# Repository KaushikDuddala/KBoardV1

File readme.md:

# KBoard

The KBoard is a simple RP2040 devboard designed from the guide!! I made some changes visually like the orientation of the chip bc lowk 45 degrees looks cooler. routing was a nightmate tho!!

## Features:

- RP2040 microcontroller  
- USB-C connector for programming/power  
- Standard pin headers

## Future Features:

- Convert to a BadUSB design
- Wi-Fi/BT support  
- Battery Support?

## Final Design

## PCB Design

## Bill of Materials (BOM)

A combined BOM including JLCPCB part numbers:

|Id|Designator|Footprint|Quantity|Designation|Supplier & Ref|JLCPCB Part #|Unit Price|
|--|----------|---------|--------|-----------|---------------|------------|----------|
|1|J3,J2|PinHeader_1x20_P2.54mm_Vertical|2|Conn_01x20||| |
|2|U1|QFN-56-1EP_7x7mm_P0.4mm_EP3.2x3.2mm|1|RP2040||C2040|$1.8330|
|3|U3|Winbond_USON-8-1EP_3x2mm_P0.5mm_EP0.2x1.6mm|1|W25Q128JVS||C2843335|$1.1730|
|4|C8,C5,C2,C11,C17,C12,C9,C7,C6,C4,C3|C_0402_1005Metric|11|0.1uF||C1525|$0.0264|
|5|R5,R7|R_0402_1005Metric|2|1K||C11702|$0.0024|
|6|C16,C15|C_0402_1005Metric|2|33pF||C1562|$0.0040|
|7|Y1|Crystal_SMD_3225-4Pin_3.2x2.5mm|1|12 MHz||C9002|$0.1290|
|8|U2|SOT-23|1|MCP1700x-330xxTT||C39051|$1.9695|
|9|SW1|SW_Push_SPST_NO_Alps_SKRK|1|SW_Push||C720477|$0.0850|
|10|R6|R_0402_1005Metric|1|10K||C25744|$0.0010|
|11|R4,R3|R_0402_1005Metric|2|27||C25100|$0.0120|
|12|R2,R1|R_0402_1005Metric|2|5.1k||C25905|$0.0020|
|13|J4|PinHeader_1x03_P2.54mm_Vertical|1|Conn_01x03||| |
|14|C14,C13|C_0402_1005Metric|2|10uF||C19702|$0.0224|
|15|C10,C1|C_0402_1005Metric|2|1uF||C52923|$0.0116|
|16|J1|USB_C_Receptacle_HRO_TYPE-C-31-M-12|1|USB_C_Receptacle_USB2.0_14P||C165948|$0.3388|

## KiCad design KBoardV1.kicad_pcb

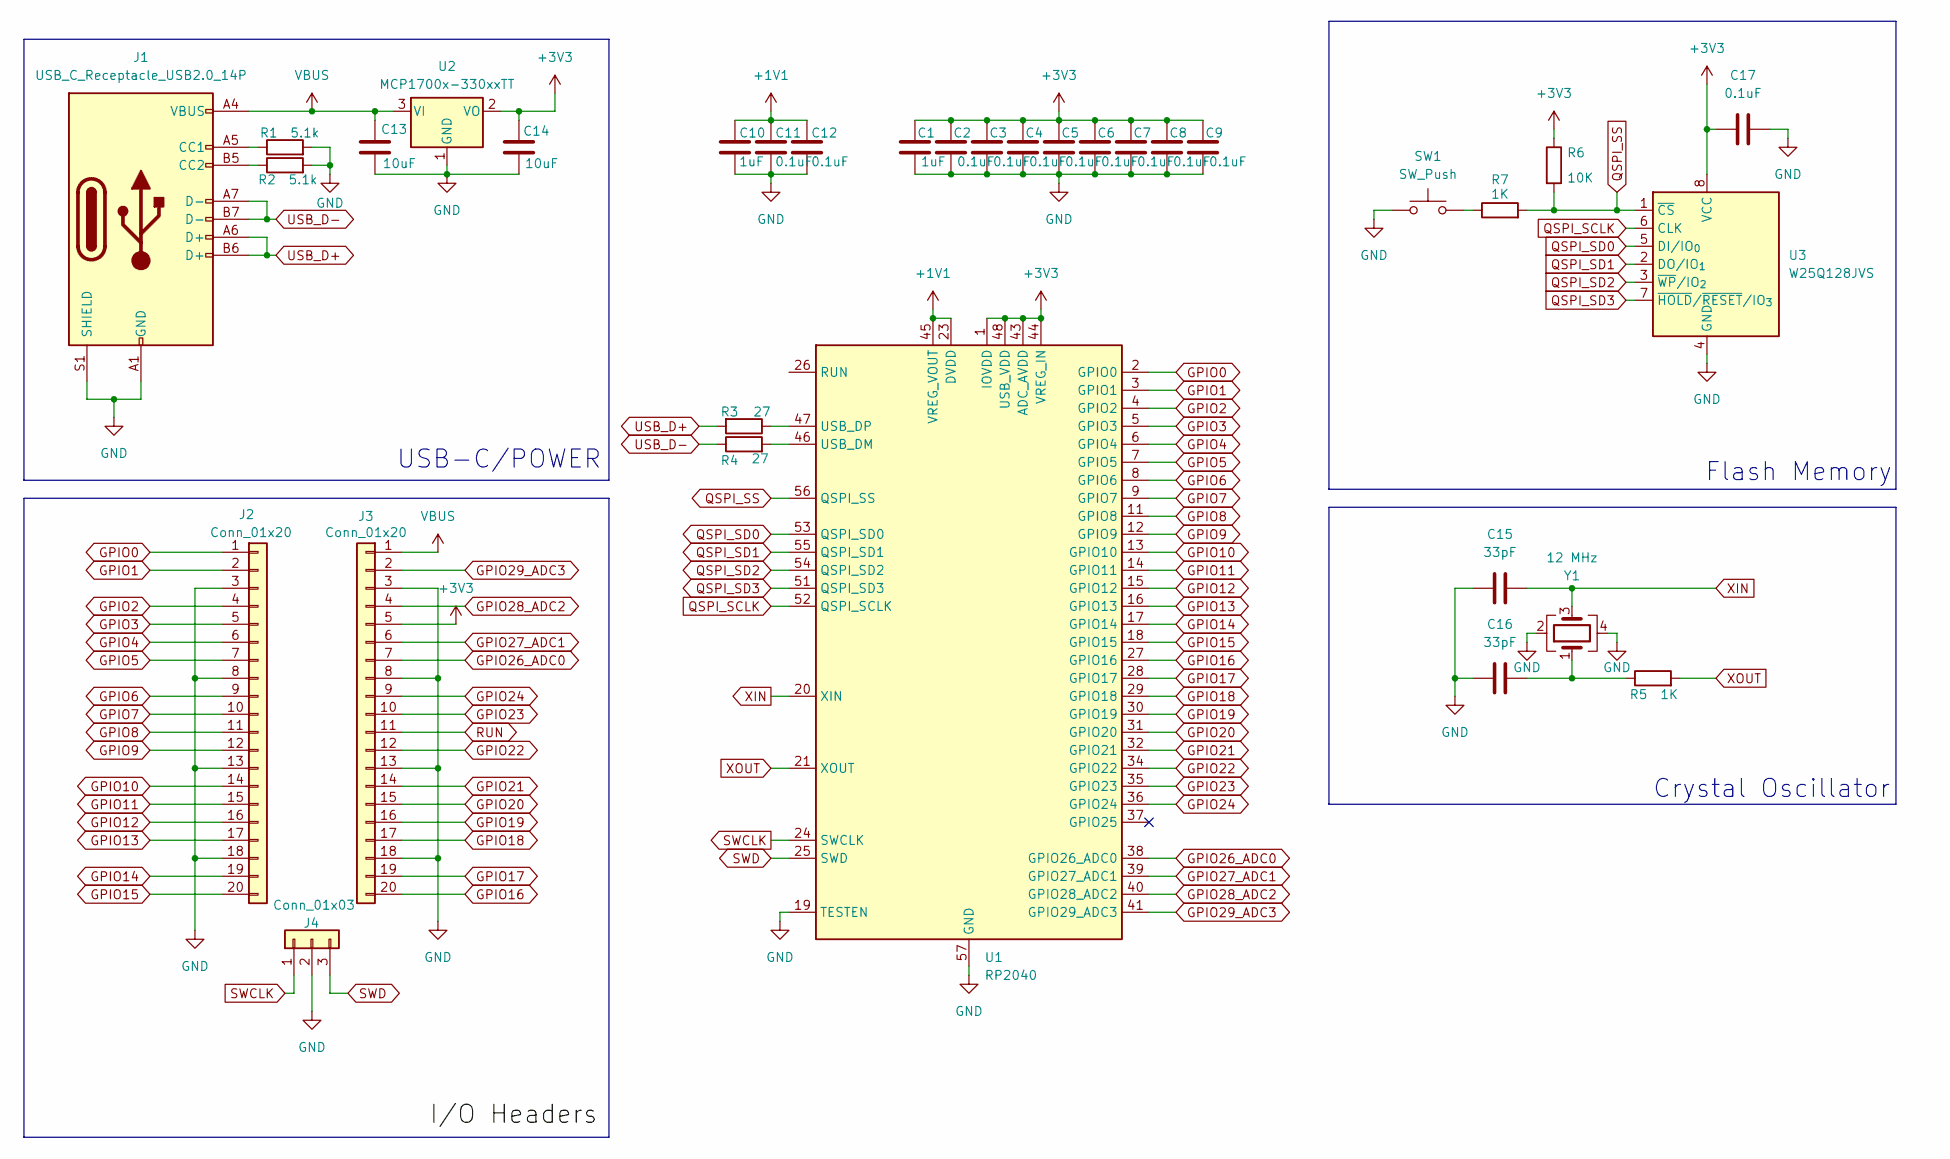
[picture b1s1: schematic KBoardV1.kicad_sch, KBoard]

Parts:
C1, C10: 1uF; C_0402_1005Metric
C2, C3, C4, C5, C6, C7, C8, C9, C11, C12, C17: 0.1uF; C_0402_1005Metric
C13, C14: 10uF; C_0402_1005Metric
C15, C16: 33pF; C_0402_1005Metric
J1: USB_C_Receptacle_USB2.0_14P; USB_C_Receptacle_HRO_TYPE-C-31-M-12
J2, J3: Conn_01x20; PinHeader_1x20_P2.54mm_Vertical
J4: Conn_01x03; PinHeader_1x03_P2.54mm_Vertical
R1, R2: 5.1k; R_0402_1005Metric
R3, R4: 27; R_0402_1005Metric
R5, R7: 1K; R_0402_1005Metric
R6: 10K; R_0402_1005Metric
SW1: SW_Push; SW_Push_SPST_NO_Alps_SKRK
U1: RP2040; QFN-56-1EP_7x7mm_P0.4mm_EP3.2x3.2mm
U2: MCP1700x-330xxTT; SOT-23
U3: W25Q128JVS; Winbond_USON-8-1EP_3x2mm_P0.5mm_EP0.2x1.6mm
Y1: 12 MHz; Crystal_SMD_3225-4Pin_3.2x2.5mm

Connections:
+1V1: C10.1, C11.1, C12.1, U1.23 (DVDD), U1.45 (VREG_VOUT), U1.50 (DVDD)
+3V3: C1.1, C2.1, C3.1, C4.1, C5.1, C6.1, C7.1, C8.1, C9.1, C14.1, C17.1, J3.5, R6.1, U1.1 (IOVDD), U1.10 (IOVDD), U1.22 (IOVDD), U1.33 (IOVDD), U1.42 (IOVDD), U1.43 (ADC_AVDD), U1.44 (VREG_IN), U1.48 (USB_VDD), U1.49 (IOVDD), U2.2 (VO), U3.8 (VCC)
GND: C1.2, C2.2, C3.2, C4.2, C5.2, C6.2, C7.2, C8.2, C9.2, C10.2, C11.2, C12.2, C13.2, C14.2, C15.1, C16.1, C17.2, J1.A1 (GND), J1.A12 (GND), J1.B1 (GND), J1.B12 (GND), J1.S1 (SHIELD), J2.3, J2.8, J2.13, J2.18, J3.3, J3.8, J3.13, J3.18, J4.2, R1.2, R2.2, SW1.1, U1.19 (TESTEN), U1.57 (GND), U2.1 (GND), U3.4 (GND), Y1.2, Y1.4
GPIO0: J2.1, U1.2 (GPIO0)
GPIO1: J2.2, U1.3 (GPIO1)
GPIO2: J2.4, U1.4 (GPIO2)
GPIO3: J2.5, U1.5 (GPIO3)
GPIO4: J2.6, U1.6 (GPIO4)
GPIO5: J2.7, U1.7 (GPIO5)
GPIO6: J2.9, U1.8 (GPIO6)
GPIO7: J2.10, U1.9 (GPIO7)
GPIO8: J2.11, U1.11 (GPIO8)
GPIO9: J2.12, U1.12 (GPIO9)
GPIO10: J2.14, U1.13 (GPIO10)
GPIO11: J2.15, U1.14 (GPIO11)
GPIO12: J2.16, U1.15 (GPIO12)
GPIO13: J2.17, U1.16 (GPIO13)
GPIO14: J2.19, U1.17 (GPIO14)
GPIO15: J2.20, U1.18 (GPIO15)
GPIO16: J3.20, U1.27 (GPIO16)
GPIO17: J3.19, U1.28 (GPIO17)
GPIO18: J3.17, U1.29 (GPIO18)
GPIO19: J3.16, U1.30 (GPIO19)
GPIO20: J3.15, U1.31 (GPIO20)
GPIO21: J3.14, U1.32 (GPIO21)
GPIO22: J3.12, U1.34 (GPIO22)
GPIO23: J3.10, U1.35 (GPIO23)
GPIO24: J3.9, U1.36 (GPIO24)
GPIO26_ADC0: J3.7, U1.38 (GPIO26_ADC0)
GPIO27_ADC1: J3.6, U1.39 (GPIO27_ADC1)
GPIO28_ADC2: J3.4, U1.40 (GPIO28_ADC2)
GPIO29_ADC3: J3.2, U1.41 (GPIO29_ADC3)
unnamed: C16.2, R5.1, Y1.1
unnamed: J1.A5 (CC1), R1.1
unnamed: J1.B5 (CC2), R2.1
unnamed: R7.1, SW1.2
unnamed: R4.2, U1.46 (USB_DM)
unnamed: R3.1, U1.47 (USB_DP)
QSPI_SCLK: U1.52 (QSPI_SCLK), U3.6 (CLK)
QSPI_SD0: U1.53 (QSPI_SD0), U3.5 (DI/IO_{0})
QSPI_SD1: U1.55 (QSPI_SD1), U3.2 (DO/IO_{1})
QSPI_SD2: U1.54 (QSPI_SD2), U3.3 (~WP/IO_{2})
QSPI_SD3: U1.51 (QSPI_SD3), U3.7 (~HOLD/~RESET/IO_{3})
QSPI_SS: R6.2, R7.2, U1.56 (QSPI_SS), U3.1 (~CS)
RUN: J3.11
SWCLK: J4.1, U1.24 (SWCLK)
SWD: J4.3, U1.25 (SWD)
USB_D+: J1.A6 (D+), J1.B6 (D+), R3.2
USB_D-: J1.A7 (D-), J1.B7 (D-), R4.1
VBUS: C13.1, J1.A4 (VBUS), J1.A9 (VBUS), J1.B4 (VBUS), J1.B9 (VBUS), J3.1, U2.3 (VI)
XIN: C15.2, U1.20 (XIN), Y1.3
XOUT: R5.2, U1.21 (XOUT)

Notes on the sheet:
USB-C/POWER
Crystal Oscillator
Flash Memory

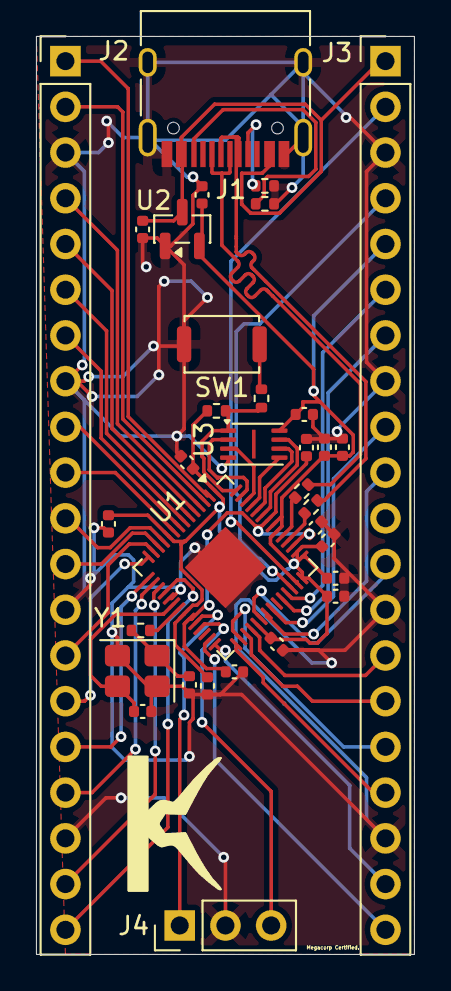
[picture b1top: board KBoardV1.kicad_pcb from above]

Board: 2 copper layers, 21.0 x 51.0 mm, 33 parts (0 on the bottom side), 51 nets.

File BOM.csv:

Id,Designator,Footprint,Quantity,Designation,Supplier & Ref,JLCPCB Part #,Unit Price
1,"J3,J2","PinHeader_1x20_P2.54mm_Vertical",2,"Conn_01x20",,,
2,U1,"QFN-56-1EP_7x7mm_P0.4mm_EP3.2x3.2mm",1,RP2040,,C2040,$1.8330
3,U3,"Winbond_USON-8-1EP_3x2mm_P0.5mm_EP0.2x1.6mm",1,W25Q128JVS,,C2843335,$1.1730
4,"C8,C5,C2,C11,C17,C12,C9,C7,C6,C4,C3","C_0402_1005Metric",11,0.1uF,,C1525,$0.0264
5,"R5,R7","R_0402_1005Metric",2,1K,,C11702,$0.0024
6,"C16,C15","C_0402_1005Metric",2,33pF,,C1562,$0.0040
7,Y1,"Crystal_SMD_3225-4Pin_3.2x2.5mm",1,12 MHz,,C9002,$0.1290
8,U2,SOT-23,1,MCP1700x-330xxTT,,C39051,$1.9695
9,SW1,"SW_Push_SPST_NO_Alps_SKRK",1,SW_Push,,C720477,$0.0850
10,R6,"R_0402_1005Metric",1,10K,,C25744,$0.0010
11,"R4,R3","R_0402_1005Metric",2,27,,C25100,$0.0120
12,"R2,R1","R_0402_1005Metric",2,5.1k,,C25905,$0.0020
13,J4,"PinHeader_1x03_P2.54mm_Vertical",1,Conn_01x03,,,
14,"C14,C13","C_0402_1005Metric",2,10uF,,C19702,$0.0224
15,"C10,C1","C_0402_1005Metric",2,1uF,,C52923,$0.0116
16,J1,"USB_C_Receptacle_HRO_TYPE-C-31-M-12",1,"USB_C_Receptacle_USB2.0_14P",,C165948,$0.3388

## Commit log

2025-12-10 reformat
2025-12-10 fix readme images
2025-12-10 fix images again
2025-12-11 fix routing and drc stuff
